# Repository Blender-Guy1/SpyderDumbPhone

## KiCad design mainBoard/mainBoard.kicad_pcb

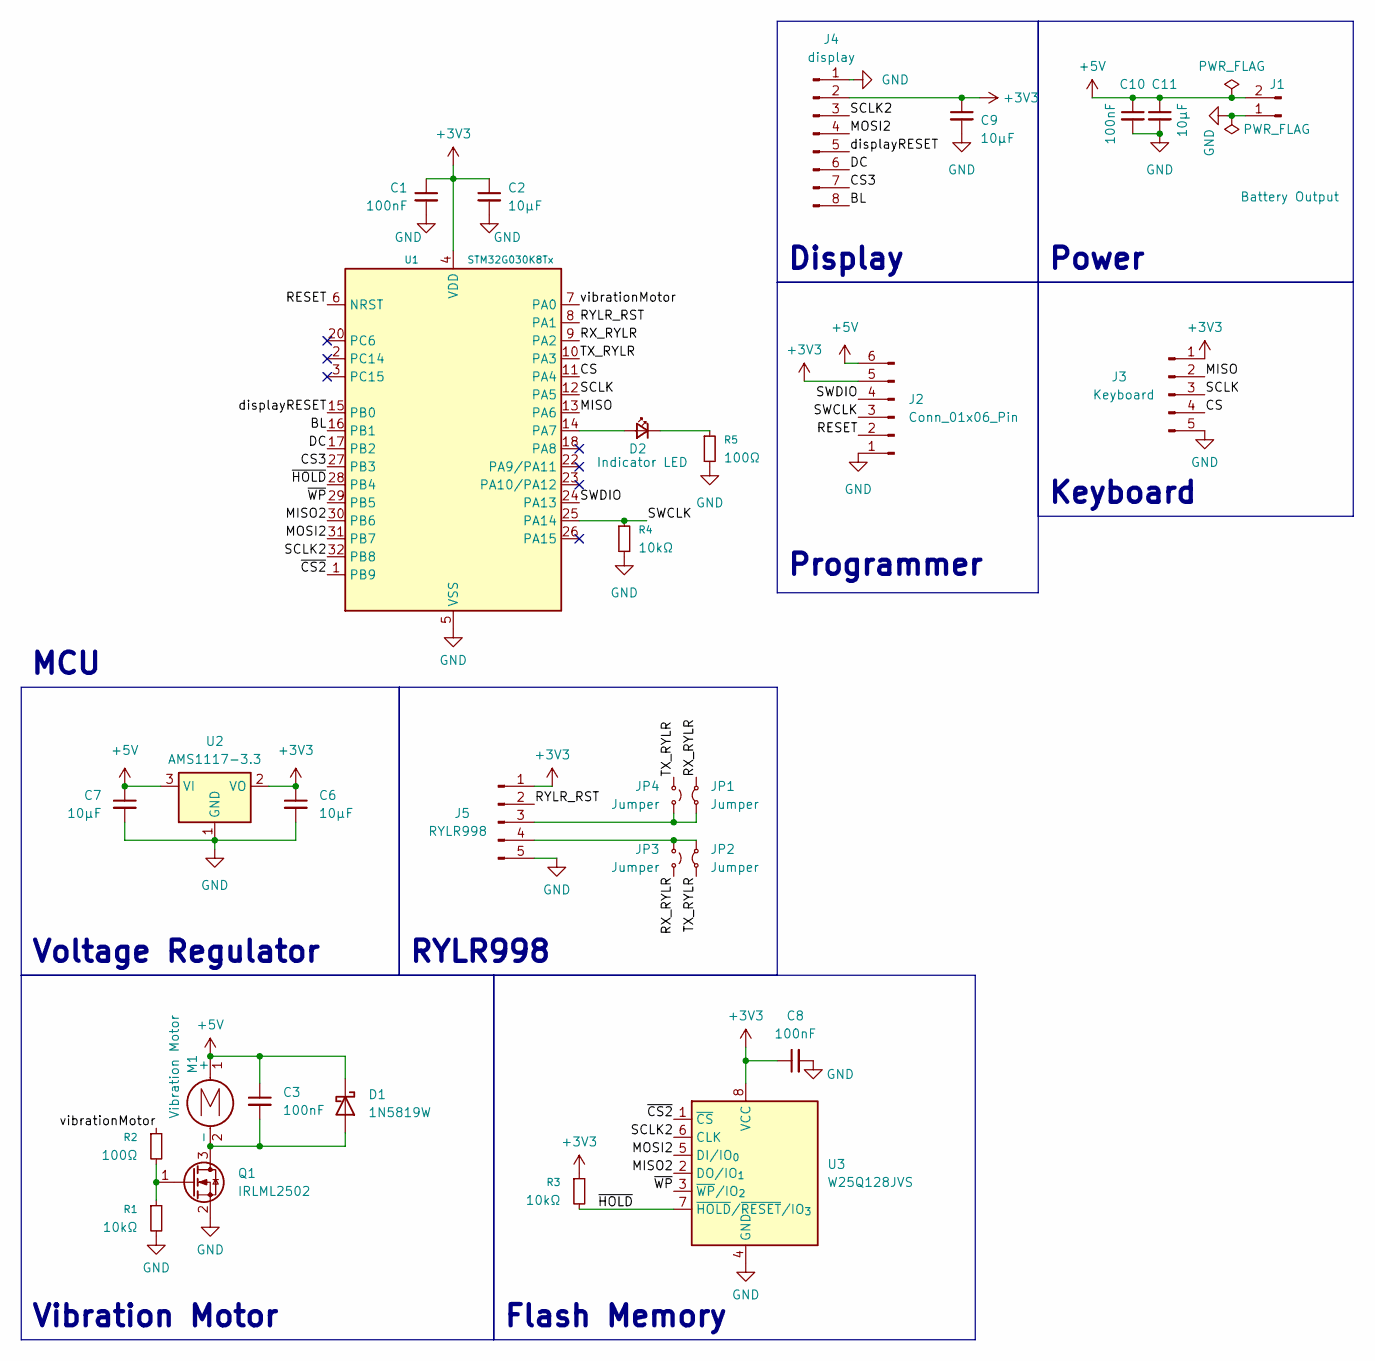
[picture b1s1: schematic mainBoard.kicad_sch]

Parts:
C1, C3, C8, C10: 100nF; C_0603_1608Metric_Pad1.08x0.95mm_HandSolder
C2, C6, C7, C9, C11: 10µF; C_0603_1608Metric_Pad1.08x0.95mm_HandSolder
D1: 1N5819W; D_SOD-323_HandSoldering
D2: Indicator LED; LED_0603_1608Metric_Pad1.05x0.95mm_HandSolder
J1: Battery Output; PinHeader_1x02_P2.54mm_Vertical
J2: Conn_01x06_Pin; PinHeader_1x06_P2.54mm_Vertical
J3: Keyboard; PinHeader_1x05_P2.54mm_Vertical
J4: display; PinHeader_1x08_P2.54mm_Vertical
J5: RYLR998; PinHeader_1x05_P2.54mm_Vertical
JP1, JP2: Jumper; SolderJumper-2_P1.3mm_Bridged_RoundedPad1.0x1.5mm
JP3, JP4: Jumper; SolderJumper-2_P1.3mm_Open_RoundedPad1.0x1.5mm
M1: Vibration Motor; PinHeader_1x02_P2.54mm_Vertical
Q1: IRLML2502; SOT-23
R1, R3, R4: 10kΩ; R_0603_1608Metric_Pad0.98x0.95mm_HandSolder
R2, R5: 100Ω; R_0603_1608Metric_Pad0.98x0.95mm_HandSolder
U1: STM32G030K8Tx; LQFP-32_7x7mm_P0.8mm
U2: AMS1117-3.3; SOT-223-3_TabPin2
U3: W25Q128JVS; SOIC-8_5.3x5.3mm_P1.27mm

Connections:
+3V3: C1.1, C2.1, C6.1, C8.1, C9.1, J2.5, J3.1, J4.2, J5.1, R3.1, U1.4 (VDD), U2.2 (VO), U3.8 (VCC)
+5V: C3.1, C7.1, C10.1, C11.1, D1.1 (K), J1.2, J2.6, M1.1 (+), U2.3 (VI)
/BL: J4.8, U1.16 (PB1)
/CS: J3.4, U1.11 (PA4)
/CS3: J4.7, U1.27 (PB3)
/DC: J4.6, U1.17 (PB2)
/MISO: J3.2, U1.13 (PA6)
/MISO2: U1.30 (PB6), U3.2 (DO/IO_{1})
/MOSI2: J4.4, U1.31 (PB7), U3.5 (DI/IO_{0})
/RESET: J2.2, U1.6 (NRST)
/RX_RYLR: JP1.2 (B), JP3.1 (A), U1.9 (PA2)
/RYLR_RST: J5.2, U1.8 (PA1)
/SCLK: J3.3, U1.12 (PA5)
/SCLK2: J4.3, U1.32 (PB8), U3.6 (CLK)
/SWCLK: J2.3, R4.1, U1.25 (PA14)
/SWDIO: J2.4, U1.24 (PA13)
/TX_RYLR: JP2.1 (A), JP4.2 (B), U1.10 (PA3)
/displayRESET: J4.5, U1.15 (PB0)
/vibrationMotor: R2.1, U1.7 (PA0)
/~CS2: U1.1 (PB9), U3.1 (~CS)
/~HOLD: R3.2, U1.28 (PB4), U3.7 (~HOLD/~RESET/IO_{3})
/~WP: U1.29 (PB5), U3.3 (~WP/IO_{2})
GND: C1.2, C2.2, C6.2, C7.2, C8.2, C9.2, C10.2, C11.2, J1.1, J2.1, J3.5, J4.1, J5.5, Q1.2 (S), R1.2, R4.2, R5.2, U1.5 (VSS), U2.1 (GND), U3.4 (GND)
unnamed: C3.2, D1.2 (A), M1.2 (-), Q1.3 (D)
unnamed: D2.2 (A), U1.14 (PA7)
unnamed: D2.1 (K), R5.1
unnamed: J5.3, JP1.1 (A), JP4.1 (A)
unnamed: J5.4, JP2.2 (B), JP3.2 (B)
unnamed: Q1.1 (G), R1.1, R2.2

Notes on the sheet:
Voltage Regulator
Power
RYLR998
Programmer
Keyboard
Display
Flash Memory
MCU
Vibration Motor

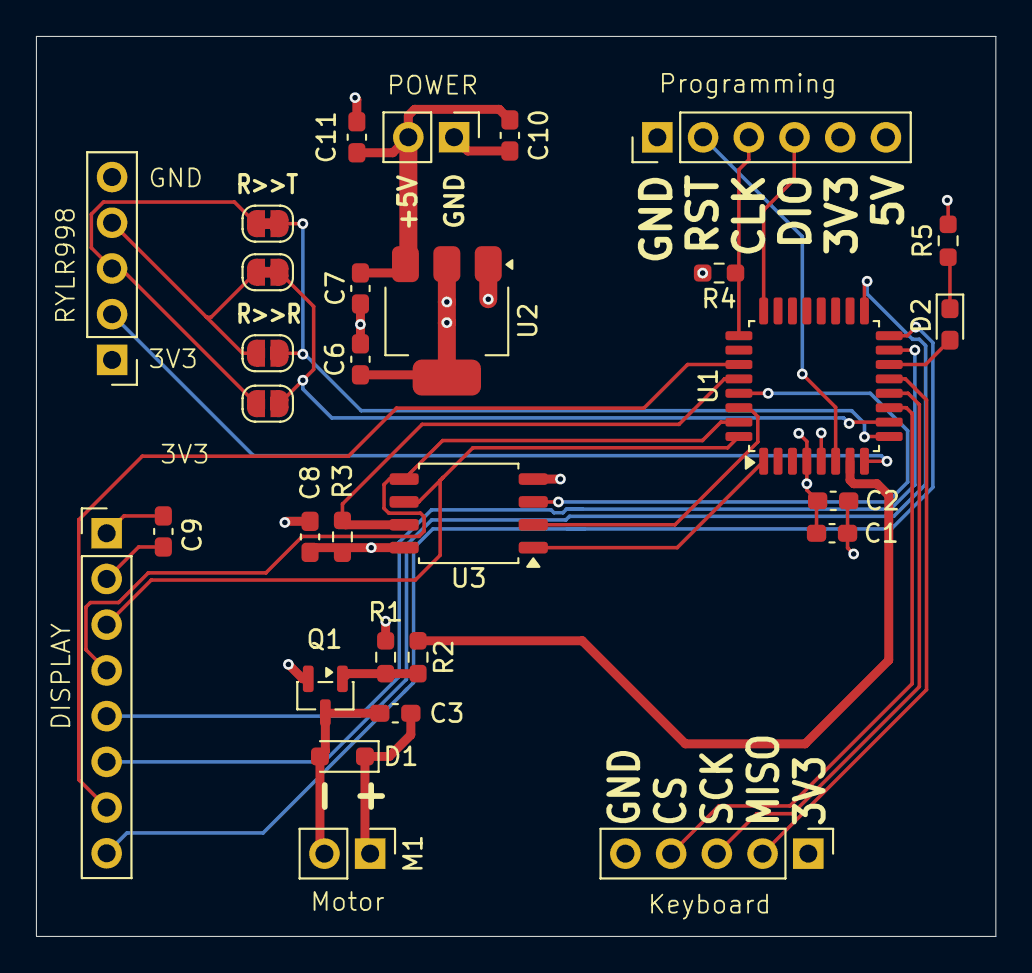
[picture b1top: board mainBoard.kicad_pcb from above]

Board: 4 copper layers, 53.3 x 50.0 mm, 30 parts (0 on the bottom side), 29 nets.

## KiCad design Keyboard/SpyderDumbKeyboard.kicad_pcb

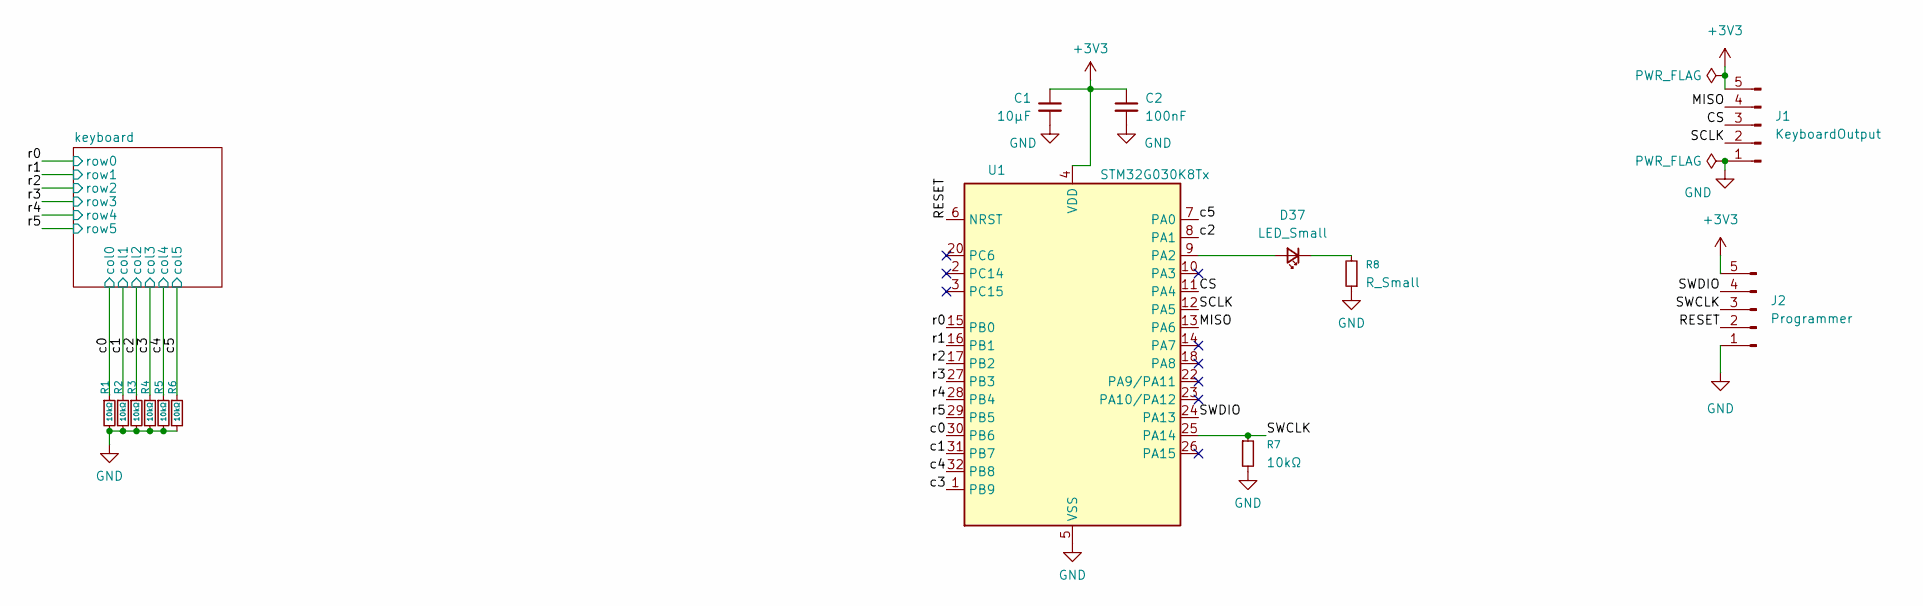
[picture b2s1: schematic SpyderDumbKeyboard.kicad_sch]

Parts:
C1: 10µF; C_0603_1608Metric_Pad1.08x0.95mm_HandSolder
C2: 100nF; C_0603_1608Metric_Pad1.08x0.95mm_HandSolder
D37: LED_Small; LED_0603_1608Metric_Pad1.05x0.95mm_HandSolder
J1: KeyboardOutput; PinHeader_1x05_P2.54mm_Vertical
J2: Programmer; PinHeader_1x05_P2.54mm_Vertical
R1, R2, R3, R4, R5, R6, R7: 10kΩ; R_0603_1608Metric_Pad0.98x0.95mm_HandSolder
R8: R_Small; R_0603_1608Metric_Pad0.98x0.95mm_HandSolder
U1: STM32G030K8Tx; LQFP-32_7x7mm_P0.8mm

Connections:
+3V3: C1.1, C2.1, J1.5, J2.5, U1.4 (VDD)
/CS: J1.3, U1.11 (PA4)
/MISO: J1.4, U1.13 (PA6)
/RESET: J2.2, U1.6 (NRST)
/SCLK: J1.2, U1.12 (PA5)
/SWCLK: J2.3, R7.1, U1.25 (PA14)
/SWDIO: J2.4, U1.24 (PA13)
/c0: R1.1, U1.30 (PB6); also elsewhere on the board
/c1: R2.1, U1.31 (PB7); also elsewhere on the board
/c2: R3.1, U1.8 (PA1); also elsewhere on the board
/c3: R4.1, U1.1 (PB9); also elsewhere on the board
/c4: R5.1, U1.32 (PB8); also elsewhere on the board
/c5: R6.1, U1.7 (PA0); also elsewhere on the board
/r0: U1.15 (PB0); also elsewhere on the board
/r1: U1.16 (PB1); also elsewhere on the board
/r2: U1.17 (PB2); also elsewhere on the board
/r3: U1.27 (PB3); also elsewhere on the board
/r4: U1.28 (PB4); also elsewhere on the board
/r5: U1.29 (PB5); also elsewhere on the board
GND: C1.2, C2.2, J1.1, J2.1, R1.2, R2.2, R3.2, R4.2, R5.2, R6.2, R7.2, R8.1, U1.5 (VSS)
unnamed: D37.2 (A), U1.9 (PA2)
unnamed: D37.1 (K), R8.2

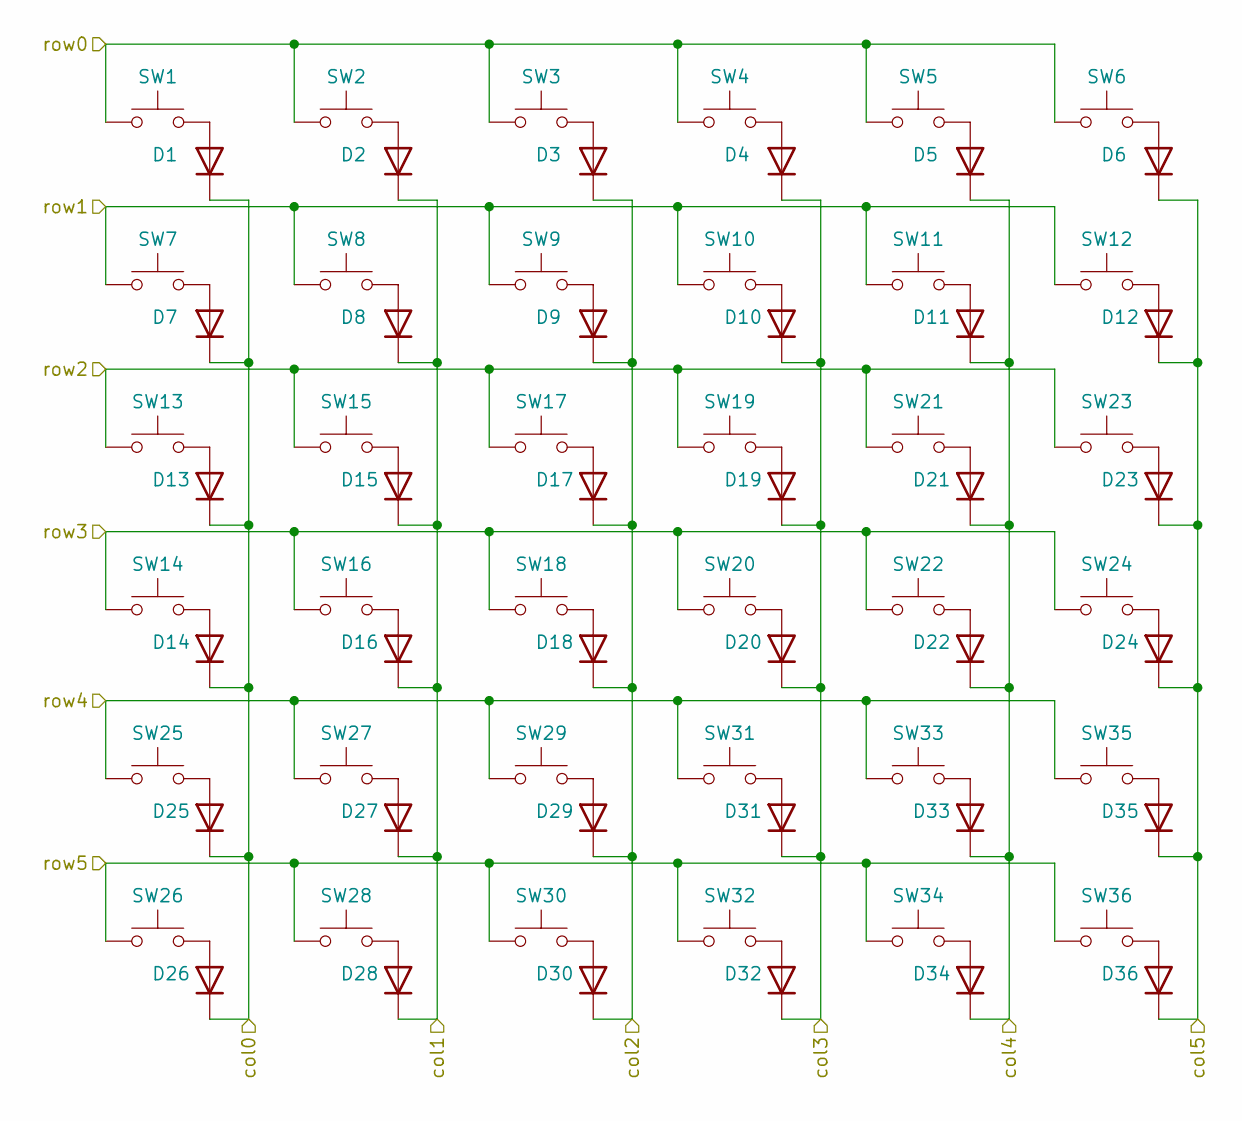
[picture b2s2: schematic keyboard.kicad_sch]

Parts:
D1, D2, D3, D4, D5, D6, D7, D8, D9, D10, D11, D12, D13, D14, D15, D16, D17, D18, D19, D20, D21, D22, D23, D24, D25, D26, D27, D28, D29, D30, D31, D32, D33, D34, D35, D36: 1N4148WS; D_SOD-323
SW1, SW2, SW3, SW4, SW5, SW6, SW7, SW8, SW9, SW10, SW11, SW12, SW13, SW14, SW15, SW16, SW17, SW18, SW19, SW20, SW21, SW22, SW23, SW24, SW25, SW26, SW27, SW28, SW29, SW30, SW31, SW32, SW33, SW34, SW35, SW36: SW_Push; SW_TL3315NF250Q

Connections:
/c0: D1.1 (K), D7.1 (K), D13.1 (K), D14.1 (K), D25.1 (K), D26.1 (K); also elsewhere on the board
/c1: D2.1 (K), D8.1 (K), D15.1 (K), D16.1 (K), D27.1 (K), D28.1 (K); also elsewhere on the board
/c2: D3.1 (K), D9.1 (K), D17.1 (K), D18.1 (K), D29.1 (K), D30.1 (K); also elsewhere on the board
/c3: D4.1 (K), D10.1 (K), D19.1 (K), D20.1 (K), D31.1 (K), D32.1 (K); also elsewhere on the board
/c4: D5.1 (K), D11.1 (K), D21.1 (K), D22.1 (K), D33.1 (K), D34.1 (K); also elsewhere on the board
/c5: D6.1 (K), D12.1 (K), D23.1 (K), D24.1 (K), D35.1 (K), D36.1 (K); also elsewhere on the board
/r0: SW1.1, SW2.1, SW3.1, SW4.1, SW5.1, SW6.1; also elsewhere on the board
/r1: SW7.1, SW8.1, SW9.1, SW10.1, SW11.1, SW12.1; also elsewhere on the board
/r2: SW13.1, SW15.1, SW17.1, SW19.1, SW21.1, SW23.1; also elsewhere on the board
/r3: SW14.1, SW16.1, SW18.1, SW20.1, SW22.1, SW24.1; also elsewhere on the board
/r4: SW25.1, SW27.1, SW29.1, SW31.1, SW33.1, SW35.1; also elsewhere on the board
/r5: SW26.1, SW28.1, SW30.1, SW32.1, SW34.1, SW36.1; also elsewhere on the board
unnamed: D1.2 (A), SW1.2
unnamed: D2.2 (A), SW2.2
unnamed: D3.2 (A), SW3.2
unnamed: D4.2 (A), SW4.2
unnamed: D5.2 (A), SW5.2
unnamed: D6.2 (A), SW6.2
unnamed: D7.2 (A), SW7.2
unnamed: D8.2 (A), SW8.2
unnamed: D9.2 (A), SW9.2
unnamed: D10.2 (A), SW10.2
unnamed: D11.2 (A), SW11.2
unnamed: D12.2 (A), SW12.2
unnamed: D13.2 (A), SW13.2
unnamed: D14.2 (A), SW14.2
unnamed: D15.2 (A), SW15.2
unnamed: D16.2 (A), SW16.2
unnamed: D17.2 (A), SW17.2
unnamed: D18.2 (A), SW18.2
unnamed: D19.2 (A), SW19.2
unnamed: D20.2 (A), SW20.2
unnamed: D21.2 (A), SW21.2
unnamed: D22.2 (A), SW22.2
unnamed: D23.2 (A), SW23.2
unnamed: D24.2 (A), SW24.2
unnamed: D25.2 (A), SW25.2
unnamed: D26.2 (A), SW26.2
unnamed: D27.2 (A), SW27.2
unnamed: D28.2 (A), SW28.2
unnamed: D29.2 (A), SW29.2
unnamed: D30.2 (A), SW30.2
unnamed: D31.2 (A), SW31.2
unnamed: D32.2 (A), SW32.2
unnamed: D33.2 (A), SW33.2
unnamed: D34.2 (A), SW34.2
unnamed: D35.2 (A), SW35.2
unnamed: D36.2 (A), SW36.2

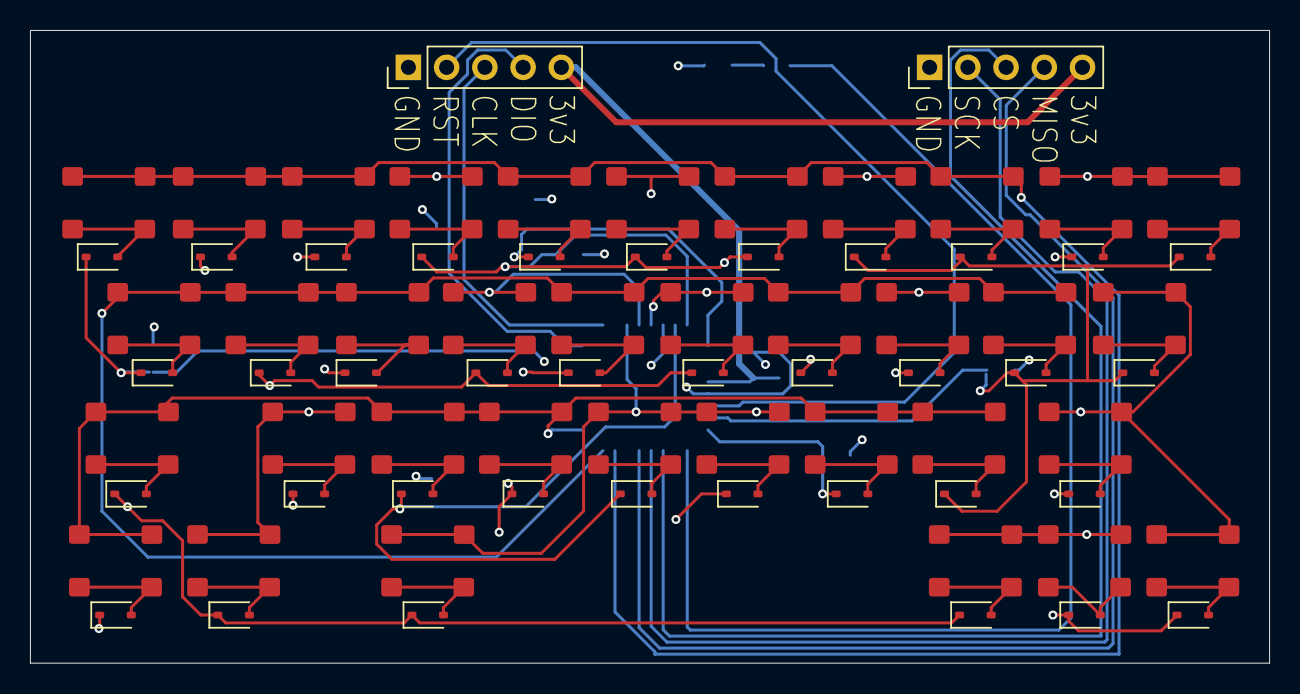
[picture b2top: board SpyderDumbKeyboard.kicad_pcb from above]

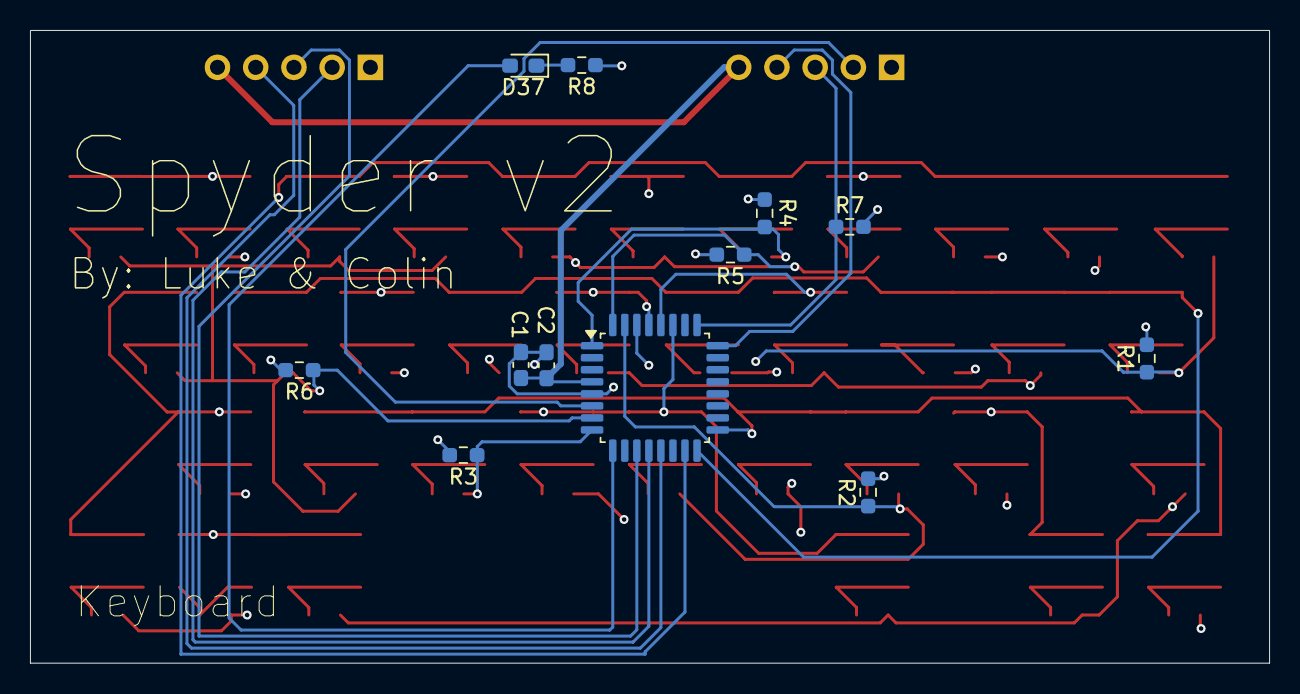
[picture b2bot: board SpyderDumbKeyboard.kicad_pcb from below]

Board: 4 copper layers, 82.3 x 42.1 mm, 86 parts (12 on the bottom side), 58 nets.

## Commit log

2026-06-13 Added Project
2026-06-13 Added Stuff
    Added Microcontroller, keyboard pins, voltage regulator, programming pins, and resonator.
2026-06-13 Added Vibration Motor & NAND Flash
2026-06-13 Added Display
2026-06-13 Connected Vibration Motor to MCU
2026-06-13 Routed PCB & fixed schematic issues
    Added RYLR, added +5v to programmer headers, added caps to display, fixed rylr reset being connected to microcontroller reset.
    Routed PCB
2026-06-13 Added Graphics
    Added version, creators, board name, and funny qr code.
2026-06-13 Fixed Minor Issue
2026-06-13 Added Keyboard
2026-06-21 Fixed minor issues & plotted gerber
